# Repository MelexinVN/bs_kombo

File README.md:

# Открытые системы беспроводной коммуникации "КомБО"

Беспроводные системы "КомБО" - проект с открытым программным и аппаратным обеспечением 
(Open source hardware)

# Open wireless communication systems "КомБО"

Wireless systems "КомБО" - a project with open software and hardware
(Open source hardware)

## Цели проекта
Целями проекта являются: разработка устройств беспроводной связи различного назначения и свободное распространение результатов этих разработок.

## Project goals
The goals of the project are: development of wireless communication devices for various purposes and free distribution of the results of these developments.

## Основные особенности проекта:
-	***Открытая лицензия***. Все материалы: исходники ПО, проекты печатных плат и 3д модели находятся в свободном доступе. 
-	***Доступные средства разработки***. Используются только бесплатные средства разработки, а также доступные материалы и компоненты.
-	***Подробная документация***. Исходники оформляются максимально подробно и документировано, чтобы их было легко изменить под свои цели. Причем документация преимущественно на русском языке (что, конечно, не принципиально, но для некоторых имеет решающее значение).

## Main features of the project:
- ***Open license***. All materials: software sources, printed circuit board designs and 3D models are freely available.
- ***Available development tools***. Only free development tools are used, as well as available materials and components.
- ***Detailed documentation***. Sources are drawn up in as much detail and documented as possible so that they can be easily changed to suit your purposes. Moreover, the documentation is predominantly in Russian (which, of course, is not essential, but for some it is of decisive importance).

## Прототипы
Ведущие и ведомое устройства собраны на микроконтроллерах ATmega8, ATmega88, ATmega328, STM32F030F4P6, ESP32 и модулях приемо-передатчика NRF24L01+. 
Программы написаны на языке СИ в средах Keil µVision v5, Microchip Studio, а также в среде Arduino IDE специально для платформы Arduino и ESP32.

## Prototypes
Master and slave devices are assembled on ATmega8, ATmega88, ATmega328, STM32F030F4P6, ESP32 microcontrollers and NRF24L01+ transceiver modules.
The programs are written in the SI language in the Keil µVision v5, Microchip Studio environments, as well as in the Arduino IDE specifically for the Arduino and ESP32 platforms.

## Содержимое репозитория
### На данный момент в репозитории можно найти:

- исходники программ и исполняемые файлы прошивок устройств;
- исходники печатных плат (проекты в Kicad), а также гербер-файлы для заказа их изготовления;

### Планируется пополнять репозиторий:
- исходниками и STL-файлами новых 3D моделей корпусов;
- специальными программами верхнего уровня для связи с ведущим устройством;
- прошивками и печатными платами для новых исполнений и применений устройств.

## Repository content
### Currently in the repository you can find:

- program sources and executable firmware files for devices;
- sources of printed circuit boards (projects in Kicad), as well as gerber files for ordering their production;

### It is planned to update the repository:
- source codes and STL files of new 3D models of cases;
- special top-level programs for communication with the master device;
- firmware and printed circuit boards for new designs and applications of devices.

## Применения
Первое готовое и оформленное применение проекта - **СИДРУ**

**С**вето-

**И**злучающее

**Д**екоративное

**Р**адиоуправляемое

**У**стройство

Описание структуры, работы, а также все материалы можно найти в [соответствующем репозитории](https://github.com/MelexinVN/bs_kombo_sidru).

## Applications
The first ready and executed application of the project - **СИДРУ**

**Light Emitting Decorative Radio Controlled Device**

A description of the structure, operation, as well as all materials can be found in the [corresponding repository](https://github.com/MelexinVN/bs_kombo_sidru).

### Электронная почта: 		    [bskombo@yandex.ru](bskombo@yandex.ru)

### Социальные сети:

- паблик ВКонтакте: 			  [vk.com/bs_kombo](https://vk.com/bs_kombo)
- Telegram-канал: 	        [t.me/bskombo](https://t.me/bskombo)
- Telegram-чат: 	          [t.me/bs_kombo_chat](https://t.me/bs_kombo_chat)

### Email: [bskombo@yandex.ru](bskombo@yandex.ru)

### Social media:

- public VKontakte: [vk.com/bs_kombo](https://vk.com/bs_kombo)
- Telegram channel: [t.me/bskombo](https://t.me/bskombo)
- Telegram chat: [t.me/bs_kombo_chat](https://t.me/bs_kombo_chat)

### Авторы всегда рады отзывам и любым конструктивным предложениям по улучшению проекта! 
### The authors are always happy to receive feedback and any constructive suggestions for improving the project!

## Лицензия
Проект распространяется под лицензией Creative Commons Attribution-ShareAlike 4.0 [CC BY-SA 4.0](https://creativecommons.org/licenses/by-sa/4.0/), 
а программное обеспечение - под лицензией GNU General Public License v3.0 [GPL-3.0 license](https://github.com/MelexinVN/bs_kombo/blob/main/LICENSE)

## License
This project is licensed under the Creative Commons 4.0 license with Attribution-ShareAlike [CC BY-SA 4.0](https://creativecommons.org/licenses/by-sa/4.0/), 
and the software is licensed under the GNU General Public License v3.0 [GPL-3.0 license](https://github.com/MelexinVN/bs_kombo/blob/main/LICENSE)

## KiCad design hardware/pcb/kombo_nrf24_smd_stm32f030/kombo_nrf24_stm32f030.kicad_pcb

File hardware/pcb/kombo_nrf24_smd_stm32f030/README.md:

### Плата для МК stm32f030f4p6 в корпусе TSSOP-20 с модулем nrf24l01+ в smd исполнении.

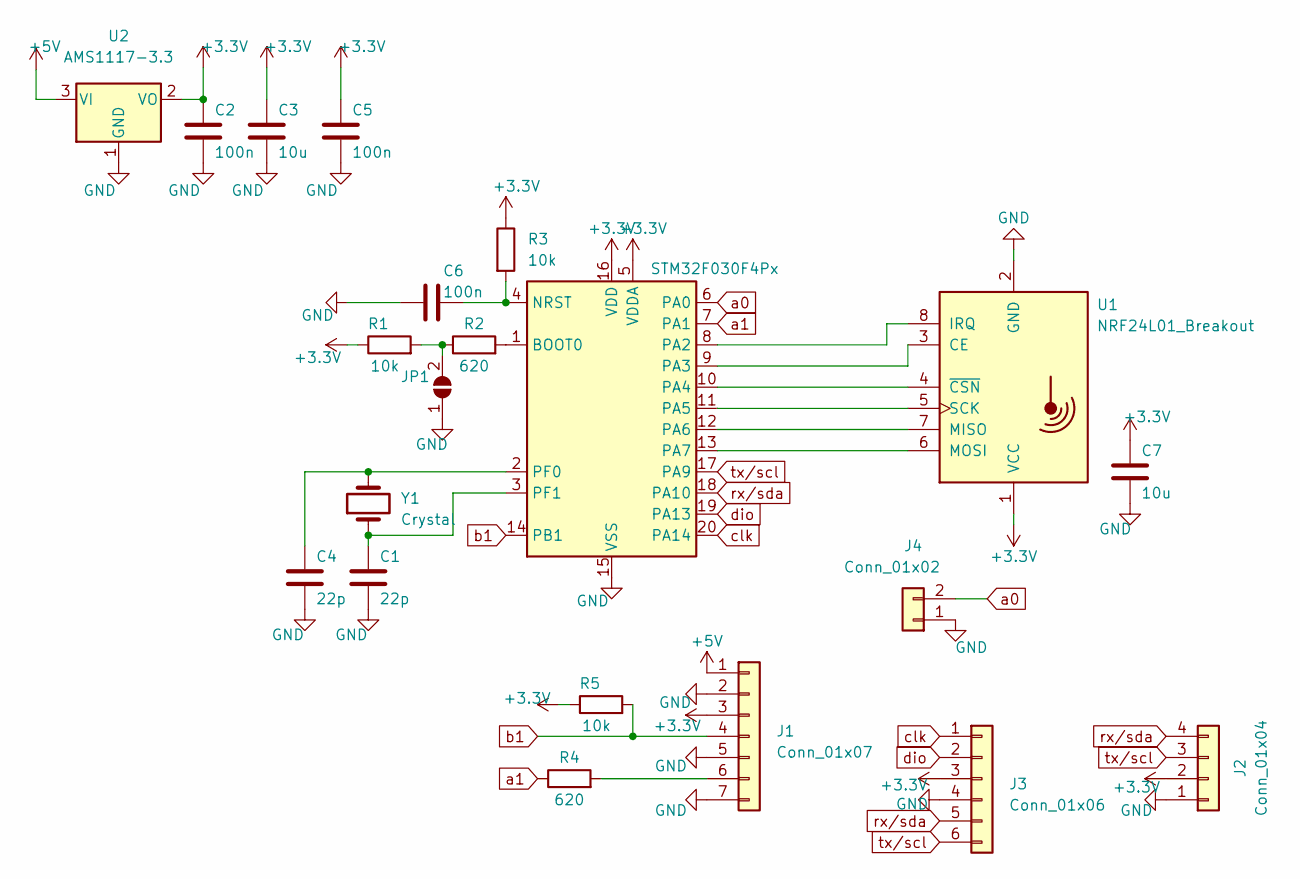
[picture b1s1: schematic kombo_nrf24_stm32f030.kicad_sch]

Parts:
C1, C4: 22p; C_0805_2012Metric_Pad1.18x1.45mm_HandSolder
C2, C5, C6: 100n; C_0805_2012Metric_Pad1.18x1.45mm_HandSolder
C3, C7: 10u; C_0805_2012Metric_Pad1.18x1.45mm_HandSolder
J1: Conn_01x07; PinHeader_1x07_P2.54mm_Vertical
J2: Conn_01x04; PinHeader_1x04_P2.54mm_Vertical
J3: Conn_01x06; PinHeader_1x06_P2.54mm_Vertical
J4: Conn_01x02; PinHeader_1x02_P2.54mm_Vertical
JP1: SolderJumper_2_Open; SolderJumper-2_P1.3mm_Open_TrianglePad1.0x1.5mm
R1, R3, R5: 10k; R_0805_2012Metric_Pad1.20x1.40mm_HandSolder
R2, R4: 620; R_0805_2012Metric_Pad1.20x1.40mm_HandSolder
U1: NRF24L01_Breakout; NRF24L01-Module-SMD
U2: AMS1117-3.3; SOT-223-3_TabPin2
U3: STM32F030F4Px; TSSOP-20_4.4x6.5mm_P0.65mm
Y1: Crystal; Crystal_HC49-U_Vertical

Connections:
+3V3: C2.1, C3.1, C5.1, C7.1, J1.3, J2.2, J3.3, R1.1, R3.1, R5.1, U1.1 (VCC), U2.2 (VO), U3.5 (VDDA), U3.16 (VDD)
+5V: J1.1, U2.3 (VI)
GND: C1.2, C2.2, C3.2, C4.2, C5.2, C6.2, C7.2, J1.2, J1.5, J1.7, J2.1, J3.4, J4.1, JP1.1 (A), U1.2 (GND), U2.1 (GND), U3.15 (VSS)
unnamed: J1.6, R4.2
unnamed: JP1.2 (B), R1.2, R2.1
unnamed: U1.3 (CE), U3.9 (PA3)
unnamed: U1.8 (IRQ), U3.8 (PA2)
unnamed: U1.7 (MISO), U3.12 (PA6)
unnamed: U1.6 (MOSI), U3.13 (PA7)
unnamed: U1.5 (SCK), U3.11 (PA5)
unnamed: U1.4 (~CSN), U3.10 (PA4)
unnamed: R2.2, U3.1 (BOOT0)
unnamed: C6.1, R3.2, U3.4 (NRST)
unnamed: C4.1, U3.2 (PF0), Y1.2
unnamed: C1.1, U3.3 (PF1), Y1.1
a0: J4.2, U3.6 (PA0)
but: J1.4, R5.2, U3.14 (PB1)
clk: J3.1, U3.20 (PA14)
dio: J3.2, U3.19 (PA13)
led: R4.1, U3.7 (PA1)
rx/sda: J2.4, J3.5, U3.18 (PA10)
tx/scl: J2.3, J3.6, U3.17 (PA9)

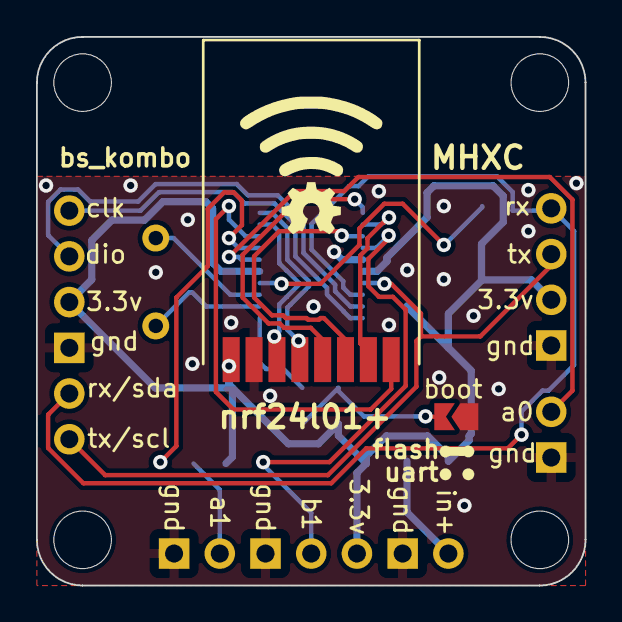
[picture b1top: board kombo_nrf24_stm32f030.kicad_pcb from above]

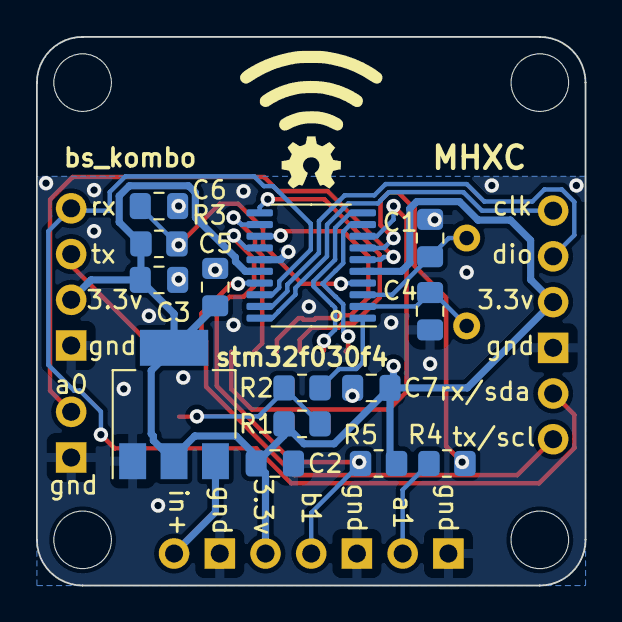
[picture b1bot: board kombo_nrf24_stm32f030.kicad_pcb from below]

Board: 2 copper layers, 30.5 x 30.5 mm, 21 parts (14 on the bottom side), 22 nets.

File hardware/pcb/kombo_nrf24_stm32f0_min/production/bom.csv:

Designator,Footprint,Quantity,Value,LCSC Part #
"C2, C5, C6",C_0805_2012Metric,3,100n,
C3,C_0805_2012Metric,1,10u,
D1,D_SOD-123,1,1N4148W,
J1,PinHeader_1x02_P2.54mm_Vertical,1,Conn_01x02,
"J2, J3, J4",PinHeader_1x04_P2.54mm_Vertical,3,Conn_01x04,
"JP1, JP2",SolderJumper-2_P1.3mm_Open_TrianglePad1.0x1.5mm,2,SolderJumper_2_Open,
"R1, R3",R_0805_2012Metric,2,10k,
R2,R_0603_1608Metric,1,620,
R4,R_0805_2012Metric,1,"4,7k",
U1,nRF24L01_Breakout,1,NRF24L01_Breakout,
U2,SOT-223-3_TabPin2,1,AMS1117-3.3,
U3,TSSOP-20_4.4x6.5mm_P0.65mm,1,STM32F030F4Px,

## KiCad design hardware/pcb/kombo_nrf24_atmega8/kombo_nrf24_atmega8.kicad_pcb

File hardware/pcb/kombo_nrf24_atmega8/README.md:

### Плата для МК ATmega8/48/88/168/328 в корпусе TQFP-32 с модулем nrf24l01+ со штырьками.
### 2 слоя.
### Расположение монтажных отверстий сделано под существующие корпуса.

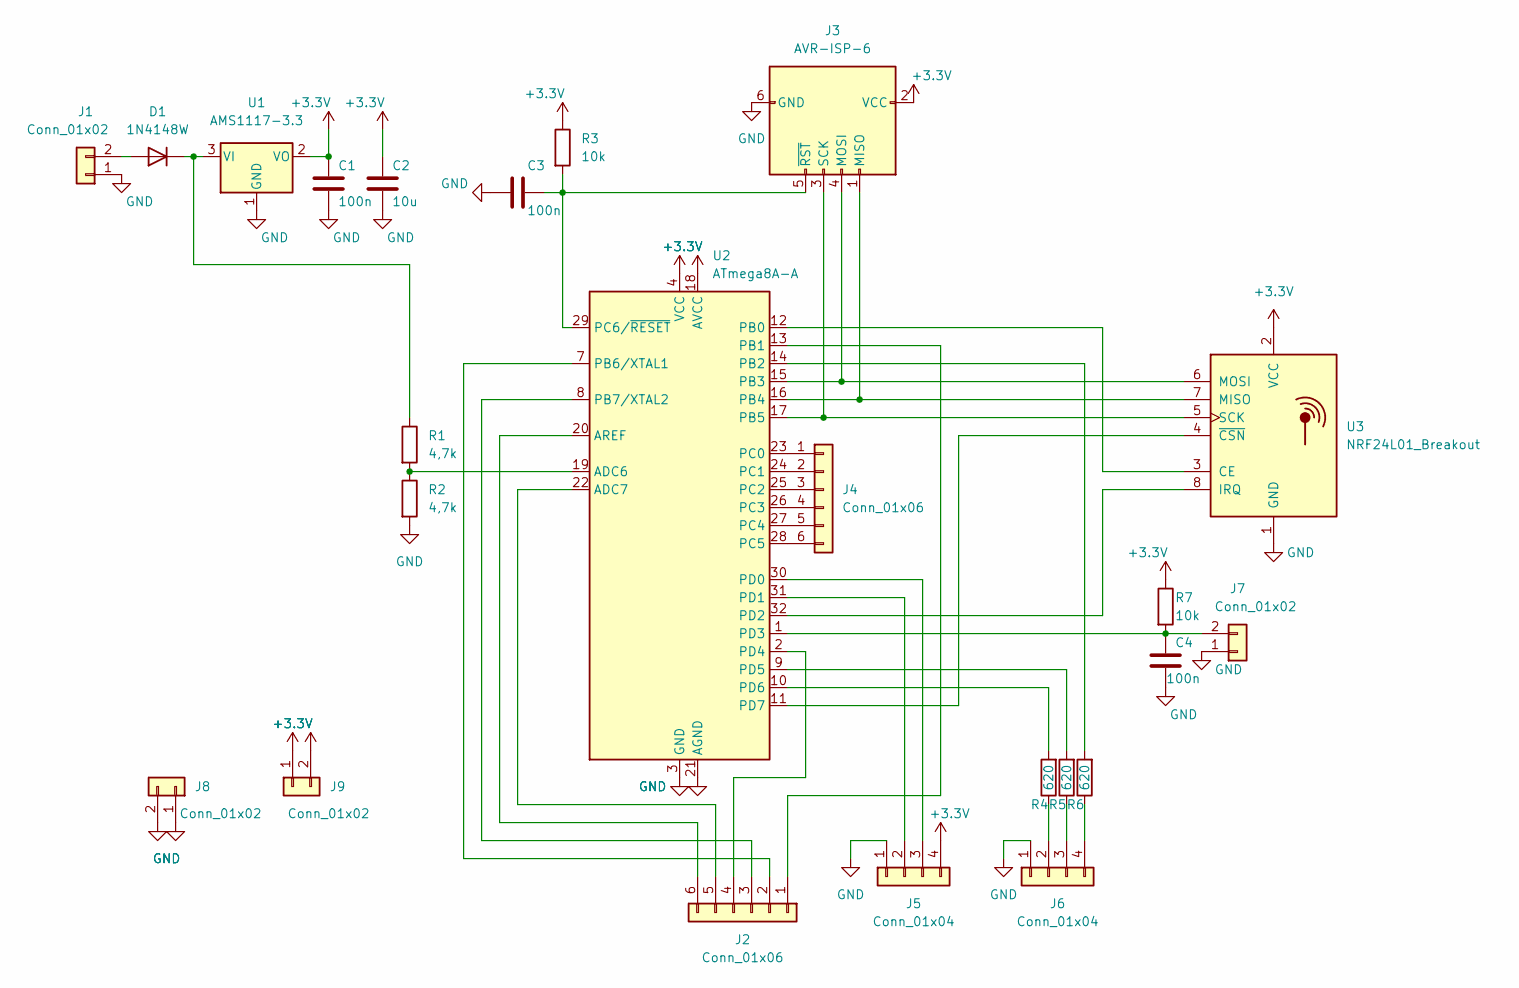
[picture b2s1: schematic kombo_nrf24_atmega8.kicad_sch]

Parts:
C1, C3, C4: 100n; C_0805_2012Metric
C2: 10u; C_0805_2012Metric
D1: 1N4148W; D_SOD-123
J1, J7, J8, J9: Conn_01x02; PinHeader_1x02_P2.54mm_Vertical
J2, J4: Conn_01x06; PinHeader_1x06_P2.54mm_Vertical
J3: AVR-ISP-6; PinHeader_2x03_P2.54mm_Vertical
J5, J6: Conn_01x04; PinHeader_1x04_P2.54mm_Vertical
R1, R2: 4,7k; R_0805_2012Metric
R3, R7: 10k; R_0805_2012Metric
R4, R5, R6: 620; R_0603_1608Metric
U1: AMS1117-3.3; SOT-223-3_TabPin2
U2: ATmega8A-A; TQFP-32_7x7mm_P0.8mm
U3: NRF24L01_Breakout; PinHeader_2x04_P2.54mm_Vertical

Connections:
+3V3: C1.1, C2.1, J3.2 (VCC), J5.4, J9.1, J9.2, R3.1, R7.1, U1.2 (VO), U2.4 (VCC), U2.6 (VCC), U2.18 (AVCC), U3.2 (VCC)
GND: C1.2, C2.2, C3.2, C4.2, J1.1, J3.6 (GND), J5.1, J6.1, J7.1, J8.1, J8.2, R2.2, U1.1 (GND), U2.3 (GND), U2.5 (GND), U2.21 (AGND), U3.1 (GND)
unnamed: C3.1, J3.5 (~RST), R3.2, U2.29 (PC6/~RESET)
unnamed: C4.1, J7.2, R7.2, U2.1 (PD3)
unnamed: D1.1 (K), R1.1, U1.3 (VI)
unnamed: D1.2 (A), J1.2
unnamed: J2.1, U2.13 (PB1)
unnamed: J2.2, U2.7 (PB6/XTAL1)
unnamed: J2.3, U2.8 (PB7/XTAL2)
unnamed: J2.4, U2.2 (PD4)
unnamed: J2.5, U2.22 (ADC7)
unnamed: J2.6, U2.20 (AREF)
unnamed: J3.1 (MISO), U2.16 (PB4), U3.7 (MISO)
unnamed: J3.3 (SCK), U2.17 (PB5), U3.5 (SCK)
unnamed: J3.4 (MOSI), U2.15 (PB3), U3.6 (MOSI)
unnamed: J4.1, U2.23 (PC0)
unnamed: J4.2, U2.24 (PC1)
unnamed: J4.3, U2.25 (PC2)
unnamed: J4.4, U2.26 (PC3)
unnamed: J4.5, U2.27 (PC4)
unnamed: J4.6, U2.28 (PC5)
unnamed: J5.2, U2.31 (PD1)
unnamed: J5.3, U2.30 (PD0)
unnamed: J6.2, R4.1
unnamed: J6.3, R5.1
unnamed: J6.4, R6.1
unnamed: R1.2, R2.1, U2.19 (ADC6)
unnamed: R4.2, U2.10 (PD6)
unnamed: R5.2, U2.9 (PD5)
unnamed: R6.2, U2.14 (PB2)
unnamed: U2.11 (PD7), U3.4 (~CSN)
unnamed: U2.12 (PB0), U3.3 (CE)
unnamed: U2.32 (PD2), U3.8 (IRQ)

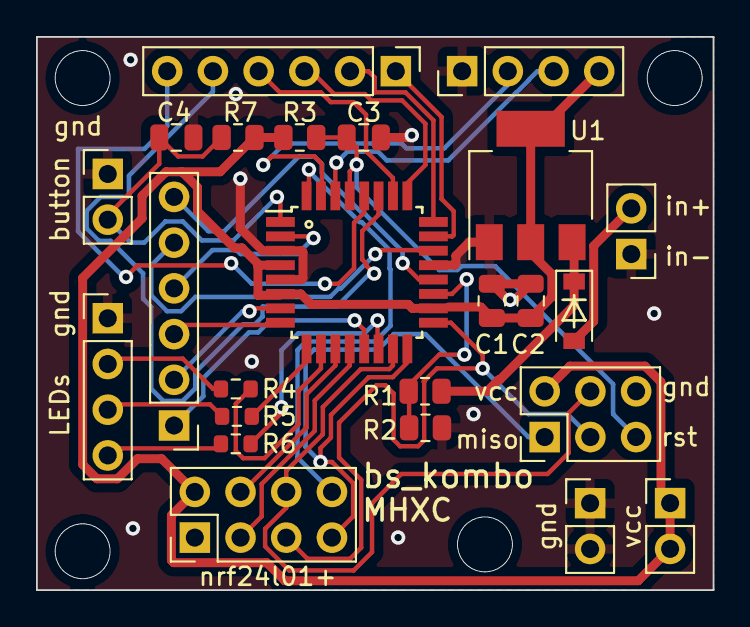
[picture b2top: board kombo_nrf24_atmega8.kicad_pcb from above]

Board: 2 copper layers, 37.6 x 30.7 mm, 24 parts (0 on the bottom side), 33 nets.

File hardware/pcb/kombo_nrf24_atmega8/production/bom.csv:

Designator,Footprint,Quantity,Value,LCSC Part #
"C1, C3, C4",C_0805_2012Metric,3,100n,
C2,C_0805_2012Metric,1,10u,
D1,D_SOD-123,1,1N4148W,
"J1, J7, J8, J9",PinHeader_1x02_P2.54mm_Vertical,4,Conn_01x02,
"J2, J4",PinHeader_1x06_P2.54mm_Vertical,2,Conn_01x06,
J3,PinHeader_2x03_P2.54mm_Vertical,1,AVR-ISP-6,
"J5, J6",PinHeader_1x04_P2.54mm_Vertical,2,Conn_01x04,
"R1, R2",R_0805_2012Metric,2,"4,7k",
"R3, R7",R_0805_2012Metric,2,10k,
"R4, R5, R6",R_0603_1608Metric,3,620,
U1,SOT-223-3_TabPin2,1,AMS1117-3.3,
U2,TQFP-32_7x7mm_P0.8mm,1,ATmega8A-A,
U3,PinHeader_2x04_P2.54mm_Vertical,1,NRF24L01_Breakout,

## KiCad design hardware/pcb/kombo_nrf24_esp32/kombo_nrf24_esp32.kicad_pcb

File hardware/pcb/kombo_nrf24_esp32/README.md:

### Плата для ESP32-WROOM с smd модулем nrf24l01+.
### Для перевода в режим загрузки прошивки нажать кнопку "EN" и отпустить при зажатой кнопке "BOOT", либо подать питание при зажатой кнопке "BOOT".

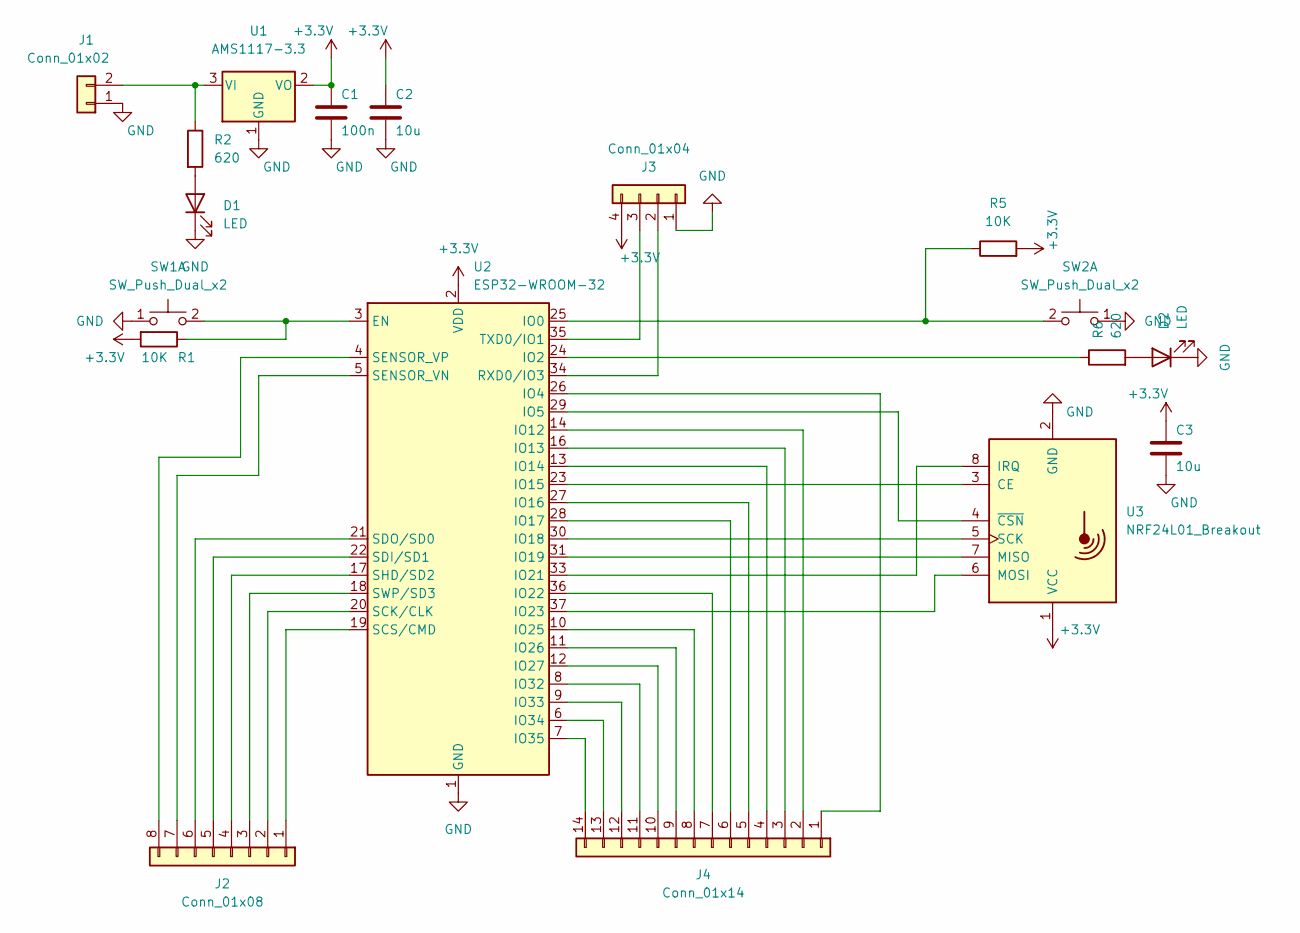
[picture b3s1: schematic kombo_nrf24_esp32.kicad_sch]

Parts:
C1: 100n; C_0805_2012Metric_Pad1.18x1.45mm_HandSolder
C2, C3: 10u; C_0805_2012Metric_Pad1.18x1.45mm_HandSolder
D1, D2: LED; LED_0805_2012Metric_Pad1.15x1.40mm_HandSolder
J1: Conn_01x02; PinHeader_1x02_P2.54mm_Vertical
J2: Conn_01x08; PinHeader_1x08_P2.54mm_Vertical
J3: Conn_01x04; PinHeader_1x04_P2.54mm_Vertical
J4: Conn_01x14; PinHeader_1x14_P2.54mm_Vertical
R1, R5: 10К; R_0805_2012Metric_Pad1.20x1.40mm_HandSolder
R2, R6: 620; R_0805_2012Metric_Pad1.20x1.40mm_HandSolder
SW1, SW2: SW_Push_Dual_x2; SW_PUSH_6mm_H4.3mm
U1: AMS1117-3.3; SOT-223-3_TabPin2
U2: ESP32-WROOM-32
U3: NRF24L01_Breakout; NRF24L01-SMD

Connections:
+3.3V: C1.1, C2.1, C3.1, J3.4, R1.2, R5.2, U1.2 (VO), U2.2 (VDD), U3.1 (VCC)
GND: C1.2, C2.2, C3.2, D1.1 (K), D2.1 (K), J1.1, J3.1, SW1.1 (C), SW2.1 (C), U1.1 (GND), U2.1 (GND), U2.15 (GND), U2.38 (GND), U2.39 (GND), U3.2 (GND)
unnamed: D1.2 (A), R2.2
unnamed: D2.2 (A), R6.2
unnamed: J1.2, R2.1, U1.3 (VI)
unnamed: J2.1, U2.19 (SCS/CMD)
unnamed: J2.2, U2.20 (SCK/CLK)
unnamed: J2.3, U2.18 (SWP/SD3)
unnamed: J2.4, U2.17 (SHD/SD2)
unnamed: J2.5, U2.22 (SDI/SD1)
unnamed: J2.6, U2.21 (SDO/SD0)
unnamed: J2.7, U2.5 (SENSOR_VN)
unnamed: J2.8, U2.4 (SENSOR_VP)
unnamed: J3.2, U2.34 (RXD0/IO3)
unnamed: J3.3, U2.35 (TXD0/IO1)
unnamed: J4.1, U2.26 (IO4)
unnamed: J4.2, U2.14 (IO12)
unnamed: J4.3, U2.16 (IO13)
unnamed: J4.4, U2.13 (IO14)
unnamed: J4.5, U2.27 (IO16)
unnamed: J4.6, U2.28 (IO17)
unnamed: J4.7, U2.36 (IO22)
unnamed: J4.8, U2.10 (IO25)
unnamed: J4.9, U2.11 (IO26)
unnamed: J4.10, U2.12 (IO27)
unnamed: J4.11, U2.8 (IO32)
unnamed: J4.12, U2.9 (IO33)
unnamed: J4.13, U2.6 (IO34)
unnamed: J4.14, U2.7 (IO35)
unnamed: R1.1, SW1.2 (D), U2.3 (EN)
unnamed: R5.1, SW2.2 (D), U2.25 (IO0)
unnamed: R6.1, U2.24 (IO2)
unnamed: U2.29 (IO5), U3.4 (~CSN)
unnamed: U2.23 (IO15), U3.3 (CE)
unnamed: U2.30 (IO18), U3.5 (SCK)
unnamed: U2.31 (IO19), U3.7 (MISO)
unnamed: U2.33 (IO21), U3.8 (IRQ)
unnamed: U2.37 (IO23), U3.6 (MOSI)

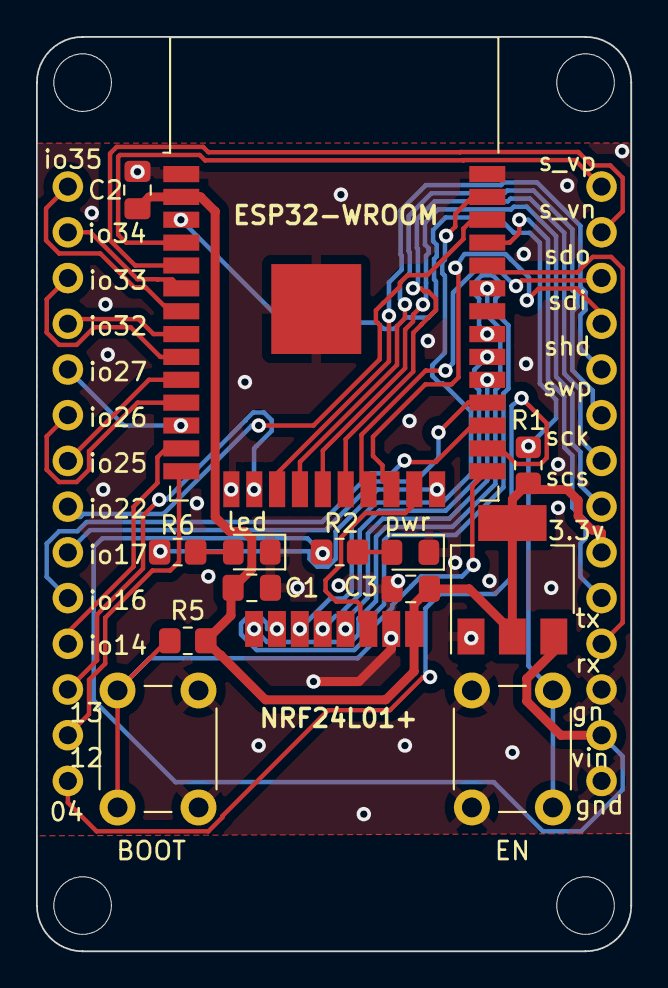
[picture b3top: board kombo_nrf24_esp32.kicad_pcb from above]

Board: 2 copper layers, 33.0 x 50.8 mm, 18 parts (0 on the bottom side), 38 nets.

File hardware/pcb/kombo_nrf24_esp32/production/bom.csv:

Designator,Footprint,Quantity,Value,LCSC Part #
C1,0805,1,100n,
"C2, C3",0805,2,10u,
"D1, D2",0805,2,LED,
J1,PinHeader_1x02_P2.54mm_Vertical,1,Conn_01x02,
J2,PinHeader_1x08_P2.54mm_Vertical,1,Conn_01x08,
J3,PinHeader_1x04_P2.54mm_Vertical,1,Conn_01x04,
J4,PinHeader_1x14_P2.54mm_Vertical,1,Conn_01x14,
"R1, R5",0805,2,10К,
"R2, R6",0805,2,620,
"SW1, SW2",SW_PUSH_6mm_H4.3mm,2,SW_Push_Dual_x2,
U1,SOT-223-3_TabPin2,1,AMS1117-3.3,
U2,ESP32-WROOM-32,1,ESP32-WROOM-32,
U3,NRF24L01-SMD,1,NRF24L01_Breakout,

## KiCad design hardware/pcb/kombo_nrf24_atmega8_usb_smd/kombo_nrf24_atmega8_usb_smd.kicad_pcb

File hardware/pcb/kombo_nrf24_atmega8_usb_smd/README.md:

### Плата для МК ATmega8/48/88/168/328 в корпусе TQFP-32 с модулем nrf24l01 в smd сполнении и с переходником uart-usb на микросхеме ch340.
### Два слоя. 
### Коннектор usb - USB-A. Плата "свисток". Программирование МК предполагается при помощи AVR-ISP-6 разъема, припаиваемого с торца платы. После прошивки можно отпаять.

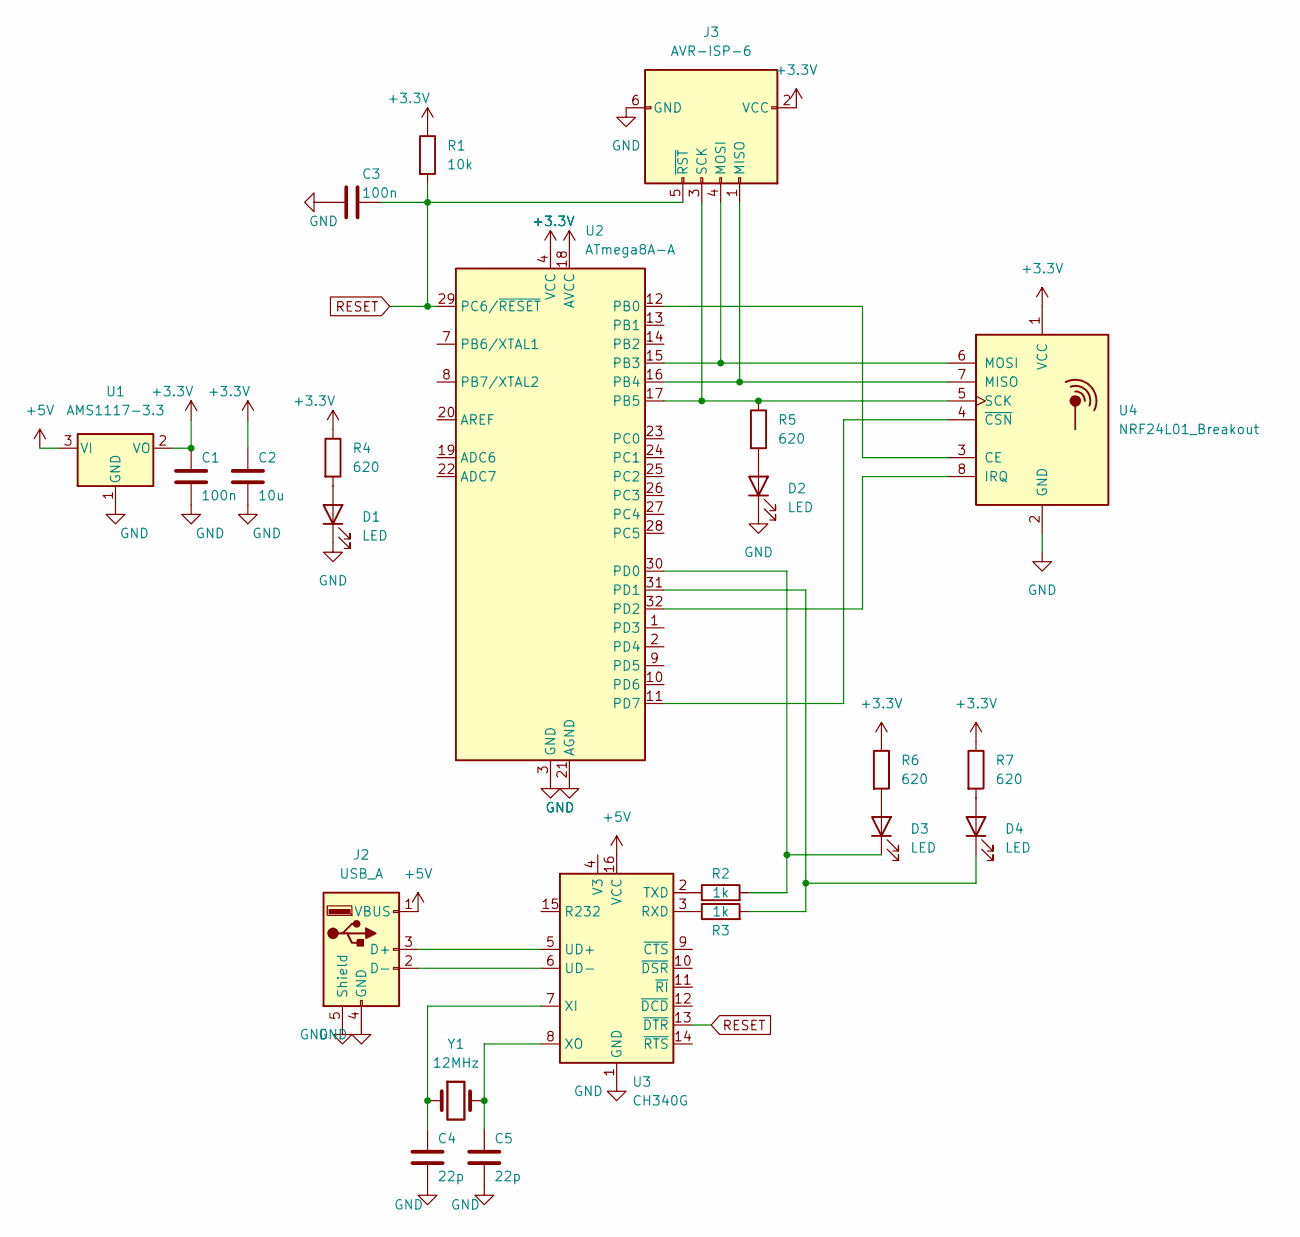
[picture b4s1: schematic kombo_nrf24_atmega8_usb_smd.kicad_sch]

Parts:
C1, C3: 100n; C_0805_2012Metric
C2: 10u; C_0805_2012Metric
C4, C5: 22p; C_0805_2012Metric
D1, D2, D3, D4: LED; LED_0805_2012Metric
J2: USB_A; USB_A_CNCTech_1001-011-01101_Horizontal
J3: AVR-ISP-6; PinHeader_2x03_P2.54mm_krai
R1: 10k; R_0805_2012Metric
R2, R3: 1k; R_0805_2012Metric
R4, R5, R6, R7: 620; R_0603_1608Metric
U1: AMS1117-3.3; SOT-223-3_TabPin2
U2: ATmega8A-A; TQFP-32_7x7mm_P0.8mm
U3: CH340G; SOIC-16_3.9x9.9mm_P1.27mm
U4: NRF24L01_Breakout; NRF24L01-Module-SMD
Y1: 12MHz; Crystal_HC49-U_Vertical

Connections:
+3V3: C1.1, C2.1, J3.2 (VCC), R1.1, R4.1, R6.1, R7.1, U1.2 (VO), U2.4 (VCC), U2.6 (VCC), U2.18 (AVCC), U4.1 (VCC)
+5V: J2.1 (VBUS), U1.3 (VI), U3.16 (VCC)
GND: C1.2, C2.2, C3.2, C4.2, C5.2, D1.1 (K), D2.1 (K), J2.4 (GND), J2.5 (Shield), J3.6 (GND), U1.1 (GND), U2.3 (GND), U2.5 (GND), U2.21 (AGND), U3.1 (GND), U4.2 (GND)
unnamed: C4.1, U3.7 (XI), Y1.1
unnamed: C5.1, U3.8 (XO), Y1.2
unnamed: D1.2 (A), R4.2
unnamed: D2.2 (A), R5.2
unnamed: D3.1 (K), R2.2, U2.30 (PD0)
unnamed: D3.2 (A), R6.2
unnamed: D4.1 (K), R3.2, U2.31 (PD1)
unnamed: D4.2 (A), R7.2
unnamed: J2.2 (D-), U3.6 (UD-)
unnamed: J2.3 (D+), U3.5 (UD+)
unnamed: J3.1 (MISO), U2.16 (PB4), U4.7 (MISO)
unnamed: J3.3 (SCK), R5.1, U2.17 (PB5), U4.5 (SCK)
unnamed: J3.4 (MOSI), U2.15 (PB3), U4.6 (MOSI)
unnamed: R2.1, U3.2 (TXD)
unnamed: R3.1, U3.3 (RXD)
unnamed: U2.11 (PD7), U4.4 (~CSN)
unnamed: U2.12 (PB0), U4.3 (CE)
unnamed: U2.32 (PD2), U4.8 (IRQ)
RESET: C3.1, J3.5 (~RST), R1.2, U2.29 (PC6/~RESET), U3.13 (~DTR)

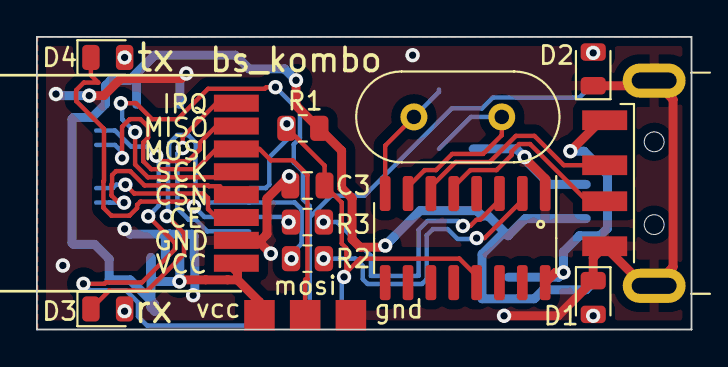
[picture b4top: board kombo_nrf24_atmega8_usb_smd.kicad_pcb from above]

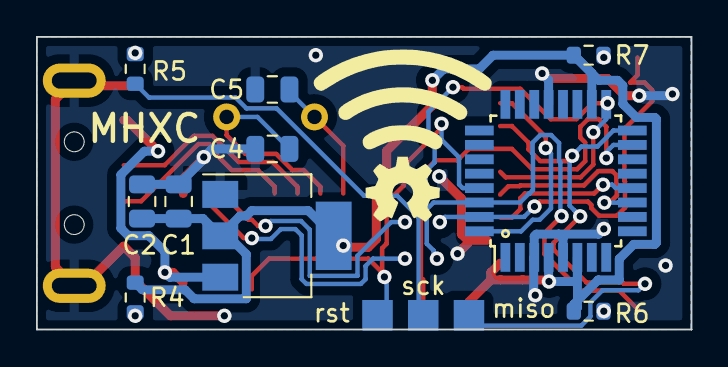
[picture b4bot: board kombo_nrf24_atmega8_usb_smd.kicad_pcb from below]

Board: 2 copper layers, 36.4 x 16.3 mm, 23 parts (11 on the bottom side), 22 nets.

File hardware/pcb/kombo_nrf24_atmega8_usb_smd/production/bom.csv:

Designator,Footprint,Quantity,Value,LCSC Part #
"C1, C3",C_0805_2012Metric,2,100n,
C2,C_0805_2012Metric,1,10u,
"C4, C5",C_0805_2012Metric,2,22p,
"D1, D2, D3, D4",LED_0805_2012Metric,4,LED,
J2,USB_A_CNCTech_1001-011-01101_Horizontal,1,USB_A,
J3,PinHeader_2x03_P2.54mm_krai,1,AVR-ISP-6,
R1,R_0805_2012Metric,1,10k,
"R2, R3",R_0805_2012Metric,2,1k,
"R4, R5, R6, R7",R_0603_1608Metric,4,620,
U1,SOT-223-3_TabPin2,1,AMS1117-3.3,
U2,TQFP-32_7x7mm_P0.8mm,1,ATmega8A-A,
U3,SOIC-16_3.9x9.9mm_P1.27mm,1,CH340G,
U4,NRF24L01-Module-SMD,1,NRF24L01_Breakout,
Y1,Crystal_HC49-U_Vertical,1,12MHz,

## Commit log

2022-12-27 27.12.2022
2023-01-10 10.01.2023
    Исправлена кодировка комментариев
2023-01-12 12.01.2023
    Откорректирован вывод отрицательных температур в программе примера базы метеодатчиков, обновлены исполнительные файлы
2023-02-05 Обновление 05.02.2023
    Добавлены примеры для микроконтроллеров stm32.
    Добавлен проект платы минимального размера для stm32f030f4p6
2023-06-23 update 23.06.2023
    Добавлен вариант с esp32
    Исправлены ошибки
2024-01-15 15/01/2024
    ✅ - обновлена библиотека работы с модулем nrf24l01+
    ✅ - добавлена библиотека работы с адресными светодиодами ws2812
    ✅ - обновлены файлы печатных плат
    ✅ - добавлены файлы печатных плат микроконтроллера stm32f030f4p6 c nrf24l01+
